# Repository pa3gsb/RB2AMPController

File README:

# Radioberry AMP Controller Board by PA3GSB

RB2AMPController (Radioberry V2.0 Amplifier Controller)

The board contains an ethernet module and a Raspberry Pi Pico (RP2040) module which implemets a TCPIP server.

The radioberry firmware talks to the controller server using a TCPIP client.

The information in the openhpsdr protocol-1 is used to control the amplifier. So if you change the frequency in your favourite SDR program the LPF filter
in the AMP will be set. Also when going into transmit; the AMP will make use of a sequencer and will switch the relais in the right order.

Information of the AMP will be placed into the protocol and will be presented in the SDR program user interface to the operator.
Information here is the temperature of the AMP, the forward and reverse power.

This controller board supports works for now only with the radioberry juice board.

## RB2AMPController-Protocol

REQUEST (to server / AMP Controller)

indentification 4bytes:	0x00 0x00 0xef 0xfe 
byte 5:  	off 	0x00 
			standby 0x0f  
			active  0xff  
byte 6:  	PTT  	0x00 	PA off.
					0xFF  	PA on.
byte 7:  	lpf  	0x00 	no LPF filter.
					0x01 	160m
					0x02 	80m
					0x03 	60m
					0x04	40m
					0x05	20m
					0x06	10m
				
Total 20 bytes (so some spare bytes)

RESPONSE (from server / AMP Controller)

identification 	4bytes:	0x00 0x00 0xef 0xfe
byte 5:			versie pa firmware  (1/10 => 0.1)  divide by 10.
byte 6, 7		temp
byte 8, 9		forwrd pwr
byte 10,11		reverse pwr
byte 12,13		u   (not implemented) 
byte 14,15		i	(not implemented) 
byte 20			error  

Total 20 bytes (so some spare bytes)

## Firmware of the RB2AMPController
The RPI pico board contains a microcontroller which need a firmware.

For loading this firmware you need to connect a USB cable to the board.
Push the button on the Pico and then plug the USB cable into your PC.
The Pico will appear as a flash drive on the PC. Then copy the file xxx.uf2 to the Pico. 

The Pico will reboot and the Pico LED will flash slowly.

### adding descriptions per port.

### Fan Control
PWM controlled FAN

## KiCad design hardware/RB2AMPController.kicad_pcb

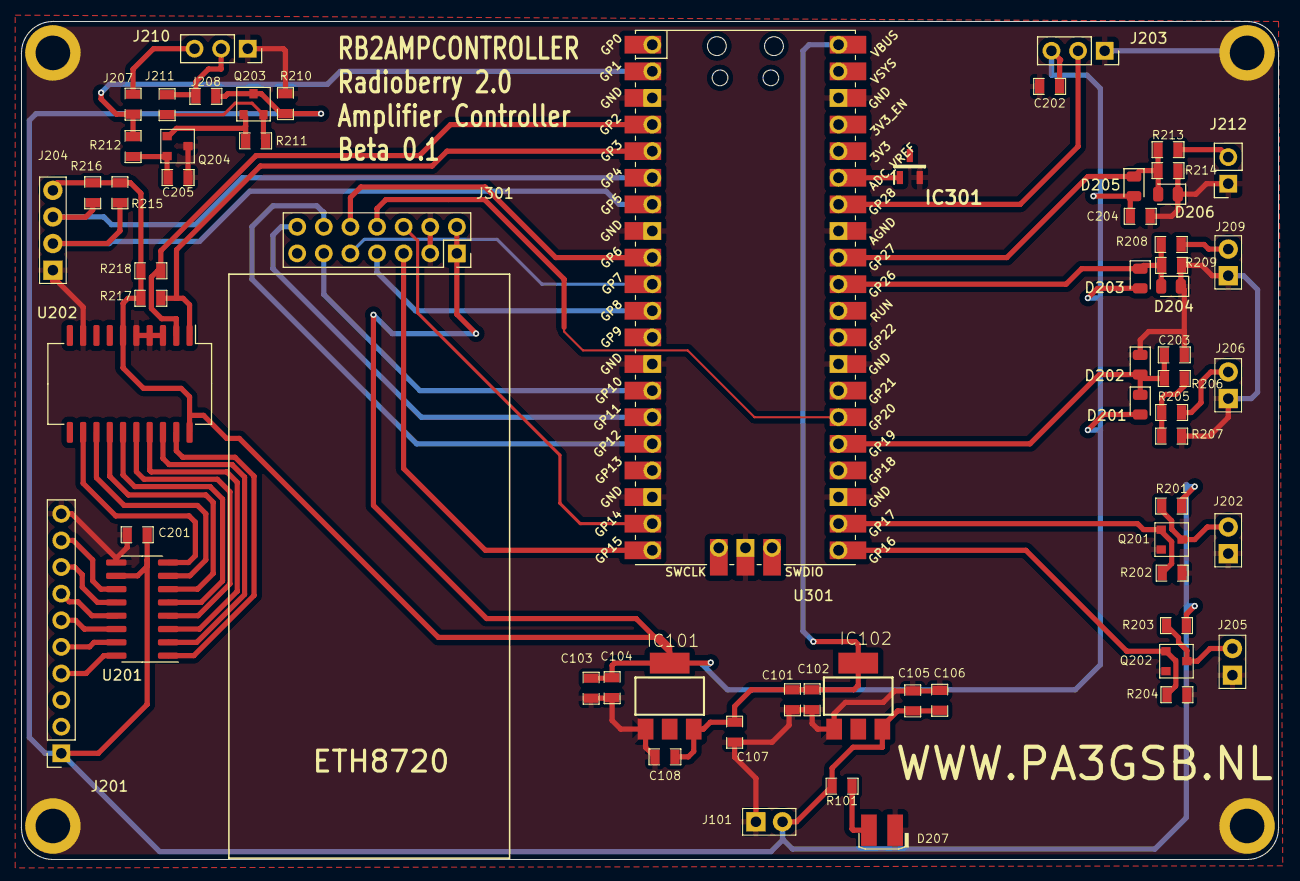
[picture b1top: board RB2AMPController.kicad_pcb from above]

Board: 2 copper layers, 120.0 x 80.0 mm, 67 parts (0 on the bottom side), 51 nets.

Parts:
C101, C105: 100pF; SMD-0805
C102, C103, C106, C107, C201, C202, C204: 100nF; SMD-0805
C104, C108: 10uF; SMD-0805
C203: 1uF; SMD-0805
C205: DNI; SMD-0805
D201, D202, D203, D204, D205, D206: DIODESCH; D_0805_2012Metric
D207: LED_Small; LED
IC101: V-REG_LD117AS33TR; V-REG_SOT223
IC102: V-REG_LD117AS50TR; V-REG_SOT223
IC301: LM4040DIM3X-3.0_NOPB; SOT95P237X112-3N
J101: +12V; 2x1
J201: LPF; PinSocket_1x10_P2.54mm_Vertical
J202: TX; 2x1
J203: Current; PinSocket_1x03_P2.54mm_Vertical
J204: Temp; 4x1
J205: BIAS; 2x1
J206: Voltage Check; 2x1
J207, J208: JNC; SMD-0805
J209: Ufwd; 2x1
J210: Fan; PinSocket_1x03_P2.54mm_Vertical
J211: DNI; SMD-0805
J212: Urev; PinSocket_1x02_P2.54mm_Vertical
J301: Eth; PinSocket_2x07_P2.54mm_Vertical
MH1, MH2, MH3, MH4: DNI; m3
Q201, Q202: MOSFET_N; SOT23_3
Q203, Q204: DNI; SOT23_3
R101: 680; SMD-0805
R201, R203, R207, R209, R214: 10K; SMD-0805
R202, R204, R215, R216, R217, R218: 4.7K; SMD-0805
R205: 330K; SMD-0805
R206: 1K; SMD-0805
R208, R213: 20K; SMD-0805
R210, R211, R212: DNI; SMD-0805
U201: ULN2803; SOIC-16_3.9x9.9mm_P1.27mm
U202: MCP23008-E_SS; SOIC-20W_7.5x15.4mm_P1.27mm
U301: Pico; RPi_Pico_SMD_TH

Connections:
+3V3: C103.1, C104.1, C202.1, C204.2, D201.2 (K), D203.2 (K), D205.2 (K), IC101.4 (OUT), J203.3, J204.4, J301.1, J301.2, R215.2, R216.2, R217.2, R218.2, U202.6 (Rst/), U202.20 (Vdd)
+5V: C101.1, C102.1, C107.1, C108.1, IC101.3 (IN), IC102.4 (OUT), U301.40 (VBUS)
+12V: C105.1, C106.1, C201.2, IC102.3 (IN), J101.2, J201.1, J208.1, Q203.3 (D), R101.1, R201.2, R203.2, R210.1, U201.10 (COM)
BIAS: Q202.1 (G), R204.2, U301.21 (GPIO16)
CRS: J301.7, U301.11 (GPIO8)
Current: J203.2, U301.34 (GPIO28_ADC2)
FAN_PWM: J207.1, R212.2, U301.2 (GPIO1)
GND: C101.2, C102.2, C103.2, C104.2, C105.2, C106.2, C107.2, C108.2, C201.1, C202.2, C203.1, C204.1, C205.2, D202.1 (A), D204.1 (A), D206.1 (A), D207.1 (K), IC101.1 (ADJ), IC102.1 (ADJ), IC301.2 (ANODE), J101.1, J201.10, J202.1, J203.1, J204.1, J205.1, J206.1, J209.1, J210.1, J212.1, J301.3, J301.4, MH1.1, MH2.1, MH3.1, MH4.1, Q201.2 (S), Q202.2 (S), Q204.3 (E), R202.1, R204.1, R207.1, R209.2, R210.2, R214.2, U201.9 (GND), U202.3 (A2), U202.4 (A1), U202.5 (A0), U202.9 (Vss), U301.3 (GND), U301.8 (GND), U301.13 (GND), U301.18 (GND), U301.23 (GND), U301.28 (GND), U301.33 (AGND), U301.38 (GND), U301.42 (GND)
I2C0 SCK: J204.2, R215.1, U301.7 (GPIO5)
I2C0 SDA: J204.3, R216.1, U301.6 (GPIO4)
I2C1 SCK: R217.1, U202.1 (SCL), U301.5 (GPIO3)
I2C1 SDA: R218.1, U202.2 (SDA), U301.4 (GPIO2)
MDC: J301.5, U301.20 (GPIO15)
MDIO: J301.6, U301.19 (GPIO14)
unnamed: D207.2 (A), R101.2
unnamed: IC301.1 (CATHODE), U301.35 (ADC_VREF)
unnamed: J201.4, U201.16 (O3)
unnamed: J201.5, U201.15 (O4)
unnamed: J201.6, U201.14 (O5)
unnamed: J201.7, U201.13 (O6)
unnamed: J201.8, U201.12 (O7)
unnamed: J201.9, U201.11 (O8)
unnamed: J202.2, Q201.3 (D), R201.1
unnamed: J205.2, Q202.3 (D), R203.1
unnamed: J206.2, R205.1
unnamed: J209.2, R208.1
unnamed: J208.2, J210.2, J211.1
unnamed: J207.2, J210.3
unnamed: J212.2, R213.1
unnamed: Q203.1 (G), Q204.1 (C), R211.2
unnamed: J211.2, Q203.2 (S), R211.1
unnamed: C205.1, Q204.2 (B), R212.1
unnamed: R205.2, R206.1, R207.2
unnamed: U201.1 (I1), U202.19 (GP7)
unnamed: U201.2 (I2), U202.18 (GP6)
unnamed: U201.3 (I3), U202.17 (GP5)
unnamed: U201.4 (I4), U202.16 (GP4)
unnamed: U201.5 (I5), U202.15 (GP3)
unnamed: U201.6 (I6), U202.14 (GP2)
unnamed: U201.7 (I7), U202.13 (GP1)
unnamed: U201.8 (I8), U202.12 (GP0)
RXCLK: J301.8, U301.26 (GPIO20)
RXD0: J301.10, U301.9 (GPIO6)
RXD1: J301.9, U301.10 (GPIO7)
TX: Q201.1 (G), R202.2, U301.22 (GPIO17)
TXD0: J301.11, U301.14 (GPIO10)
TXD1: J301.14, U301.15 (GPIO11)
TX_EN: J301.12, U301.16 (GPIO12)
UFWD: D203.1 (A), D204.2 (K), R208.2, R209.1, U301.31 (GPIO26_ADC0)
Urev: D205.1 (A), D206.2 (K), R213.2, R214.1, U301.32 (GPIO27_ADC1)
VoltCheck: C203.2, D201.1 (A), D202.2 (K), R206.2, U301.25 (GPIO19)

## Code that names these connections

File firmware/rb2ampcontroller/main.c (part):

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#endif

const uint LED_PIN = PICO_DEFAULT_LED_PIN;
const uint BIAS_PIN = 16U;
const uint RELAIS_PIN = 17U;
const uint PWM_PIN = 1;

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        sleep_ms(15);
        gpio_put(RELAIS_PIN, 1);
        sleep_ms(15);
        gpio_put(BIAS_PIN, 1); 
        actualAmpState = TX_ON;
    }      
 }
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    //sequencer
    if (actualAmpState == TX_ON) {
        sleep_ms(15);
        gpio_put(BIAS_PIN, 0);
        sleep_ms(15);
        gpio_put(RELAIS_PIN, 0);
        actualAmpState = TX_OFF;
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
int main() {
	// initialiseer IO
    gpio_init(BIAS_PIN);
    gpio_set_dir(BIAS_PIN, GPIO_OUT);
    gpio_put(BIAS_PIN, 0);
    gpio_init(RELAIS_PIN);
    gpio_set_dir(RELAIS_PIN, GPIO_OUT);
    gpio_put(RELAIS_PIN, 0);
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    struct netif_rmii_ethernet_config netif_config = {
        pio0, // PIO:            0
        0,    // pio SM:         0 and 1
        6,    // rx pin start:   6, 7, 8    => RX0, RX1, CRS
        10,   // tx pin start:   10, 11, 12 => TX0, TX1, TX-EN
        14,   // mdio pin start: 14, 15   => ?MDIO, MDC
        NULL, // MAC address (optional - NULL generates one based on flash id) 
    };

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    gpio_put(LED_PIN, 0);

    // initialiseer IO
    gpio_init(BIAS_PIN);
    gpio_set_dir(BIAS_PIN, GPIO_OUT);
    gpio_put(BIAS_PIN, 0);
    gpio_init(RELAIS_PIN);
    gpio_set_dir(RELAIS_PIN, GPIO_OUT);
    gpio_put(RELAIS_PIN, 0);
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
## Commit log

2023-10-14 small update
2023-10-18 inital firmware
2024-04-19 oeps some pending changes
2024-08-25 added the defines for i2c
